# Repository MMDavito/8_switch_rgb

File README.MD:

# Table of contents
- [Table of contents](#table-of-contents)
- [1.1 Introduction:](#11-introduction)
- [1.2 Demonstration:](#12-demonstration)
  - [1.2.1 English:](#121-english)
  - [1.2.1 Swedish:](#121-swedish)
- [2 Design and process:](#2-design-and-process)
  - [2.1 Arduino](#21-arduino)
  - [2.2 KiCad](#22-kicad)
    - [2.2.1 Schematics and details:](#221-schematics-and-details)
      - [2.2.1.1 PCB rev0](#2211-pcb-rev0)
      - [2.2.1.2 PCB rev1](#2212-pcb-rev1)
    - [2.2.2 Custom Footprint SPDT-Switch:](#222-custom-footprint-spdt-switch)
    - [2.2.3 Custom Footprint 7-segment Display:](#223-custom-footprint-7-segment-display)
  - [2.3 FreeCAD](#23-freecad)
- [3 Assembly:](#3-assembly)
  - [3.1 Assembly of frame/stand:](#31-assembly-of-framestand)
  - [3.2 Assembly/soldering of the PCB](#32-assemblysoldering-of-the-pcb)
    - [3.2.1 Resistors required:](#321-resistors-required)
    - [3.2.2 Order of assembly:](#322-order-of-assembly)
- [4 Programming and bootloading:](#4-programming-and-bootloading)
  - [4.1 Bootloading:](#41-bootloading)
  - [4.2 Programming:](#42-programming)
  - [4.3 Programming the MCU for PCB Revision 1:](#43-programming-the-mcu-for-pcb-revision-1)

________________

# 1.1 Introduction:
This project was created to teach my niece the wonders of electricity and programming.
Here is a video trying to give and project overview and explain the process that made me go from 64 bit memory board to a "space-machine":<br>

# 1.2 Demonstration: 
## 1.2.1 English:
Using Revision 0:<br>

## 1.2.1 Swedish:
Better quality than the english one, using PCB revision 1:

___________
# 2 Design and process:
## 2.1 Arduino
No real design was put in here since the issues needing solving where clearly limited and modular in its nature, the process I choose was to solve issues limited in scope and carry out experiments with components in as modular of a manner as possible.
This is how the original prototype described in the video above ended up containing 3 ATmega-328's.

This approach did however result in many .ino files and duplicate code. The decision I made was to keep all of them; this will allow me to return 5-10 years from now and realize my process of thinking and working has changed and how, maybe I will write a book or blog-post about it. 

## 2.2 KiCad
### 2.2.1 Schematics and details:
The only major differences between the two schematics are that I have a filter on the data and clock-lines in revision 1. I also relabeled the decimal-displays from order "dec-2" to "dec-0" starting from upper left corner in revision 0, to the reversed (and ISO-standard) way of counting/indexing from 0 in the upper left corner.

I also left-out the fuse and some other things in order to conserve space.
#### 2.2.1.1 PCB rev0
Will not publish Gerbers because this version should never ever be built or produced, as can be viewed in this 30 second clip:

#### 2.2.1.2 PCB rev1
Gerbers available for order in this directory:
https://github.com/MMDavito/8_switch_rgb/tree/master/KiCad/8_switch_rgb_pcb_revision_1/gerber_to_order

### 2.2.2 Custom Footprint SPDT-Switch:
The SPDT switch was purchased from digikey: https://www.digikey.se/sv/products/detail/adam-tech/SW-T3-2B-A-A3-S1/15284416 <br>
And later electrokit: https://www.electrokit.com/vippomkopplare-sub-miniatyr-1-pol-on-on-lodoron-smts-102

These had to be changed, since the footprints I found where for the larger 6-Amp switch. If I where to refactor the PCB I would probably make the soldering-pads 20% larger for this footprint, or even more if DRC/Design-Rules-Checker would allow it.
The custom footprint can be found here: https://github.com/MMDavito/8_switch_rgb/tree/master/KiCad/resources/Switch_Custom.pretty
### 2.2.3 Custom Footprint 7-segment Display:
The display used was a 14mm CA display purchased in RED here: https://www.electrokit.com/en/led-display-7-seg-14mm-superrod-ca <br>
And green from here: https://www.electrokit.com/en/led-display-7-seg-14mm-gron-ca

The schematics, PCB and footprint label it as a HDSP-511, which is incorrect, buying HDSP-511 would lead to buying a display too tall and wide to fit.
The edited footprint and 3D .step file can be found here:
https://github.com/MMDavito/8_switch_rgb/tree/master/KiCad/resources/HDSP-511Y
## 2.3 FreeCAD
What started as a means to an end of making it simpler to mount the PCB to a piece of plywood ended up resulting in 4 different design for holders and 3-5 different tools for making assembly simpler.

This process and designs are detailed in this readme:
https://github.com/MMDavito/8_switch_rgb/tree/master/FreeCad/README.MD
____________
# 3 Assembly:
## 3.1 Assembly of frame/stand:
More clear information and details about the 3d-printed parts found in the following video can be found in [this readme](./FreeCad/README.MD), section [3.3](./FreeCad/README.MD#33-template-to-mark-drill-holes) and [3.4](./FreeCad/README.MD#34-led-matrix-holder).<br>

## 3.2 Assembly/soldering of the PCB

### 3.2.1 Resistors required:
__1/8 watt resistors:__
* 10kΩ * 14
* 33Ω * 8
  
__1/4 watt resistors:__
* 330Ω * 2
* 220Ω * 8
* 1kΩ * 6

### 3.2.2 Order of assembly:
1. Small resistors (1/8 watt).
2. Big resistors (1/4 watt).
3. 3mm LED:s.
4. Transistors.
5. DIL-holders.
6. Toggle switches.
7. 7-segment displays.
8. DC-plug & screw-terminals.
9. Push-button, crystal & capacitors.
_____________
# 4 Programming and bootloading:
I used this library to allow me to install bootloader and program the ATmega https://github.com/MCUdude/MiniCore
## 4.1 Bootloading:
To get the ATmega328 become programmable one needs to install a bootloader to it:<br><br>
Here is the instruction I used: https://www.instructables.com/How-to-Burn-the-Arduino-BootLoader-on-to-a-AtMega3/

Here is a alternative version: https://www.instructables.com/Burning-the-Bootloader-on-ATMega328-using-Arduino-/

In future I might adjust the board I have made from a prototype-board or order a PCB that allow me to not need a arduino UNO connected with dupont-wires to install the bootloader to the ATmega-328.

## 4.2 Programming:
Somehow I managed to program the board using diagrams and information found on this page:
https://www.instructables.com/USB-to-Serial-TTL-Adapter-to-Program-ATmega328p/

And this video: 
https://youtu.be/tiETAwkxnmw?si=Nhqw3l6RTYwrkvaB

Skimming through above links I realize that neither really shows my process of programming the MCUs, and I should probably order a PCB and create a project to detail this.

Until I find the time for creating that PCB I here bellow attach a picture comparing the breadboard vs with the soldered prototype one.

I later attached the prototype-board to a piece of plywood to make it even more robust.

## 4.3 Programming the MCU for PCB Revision 1:
Using above instructions, load this sketch onto the MCU:
https://github.com/MMDavito/8_switch_rgb/blob/master/troubleshooting_and_revision_1/2024-03-07_8_switch_rgb_pcb_rev1/8_switch_rgb_rev_1_master_control/8_switch_rgb_rev_1_master_control.ino

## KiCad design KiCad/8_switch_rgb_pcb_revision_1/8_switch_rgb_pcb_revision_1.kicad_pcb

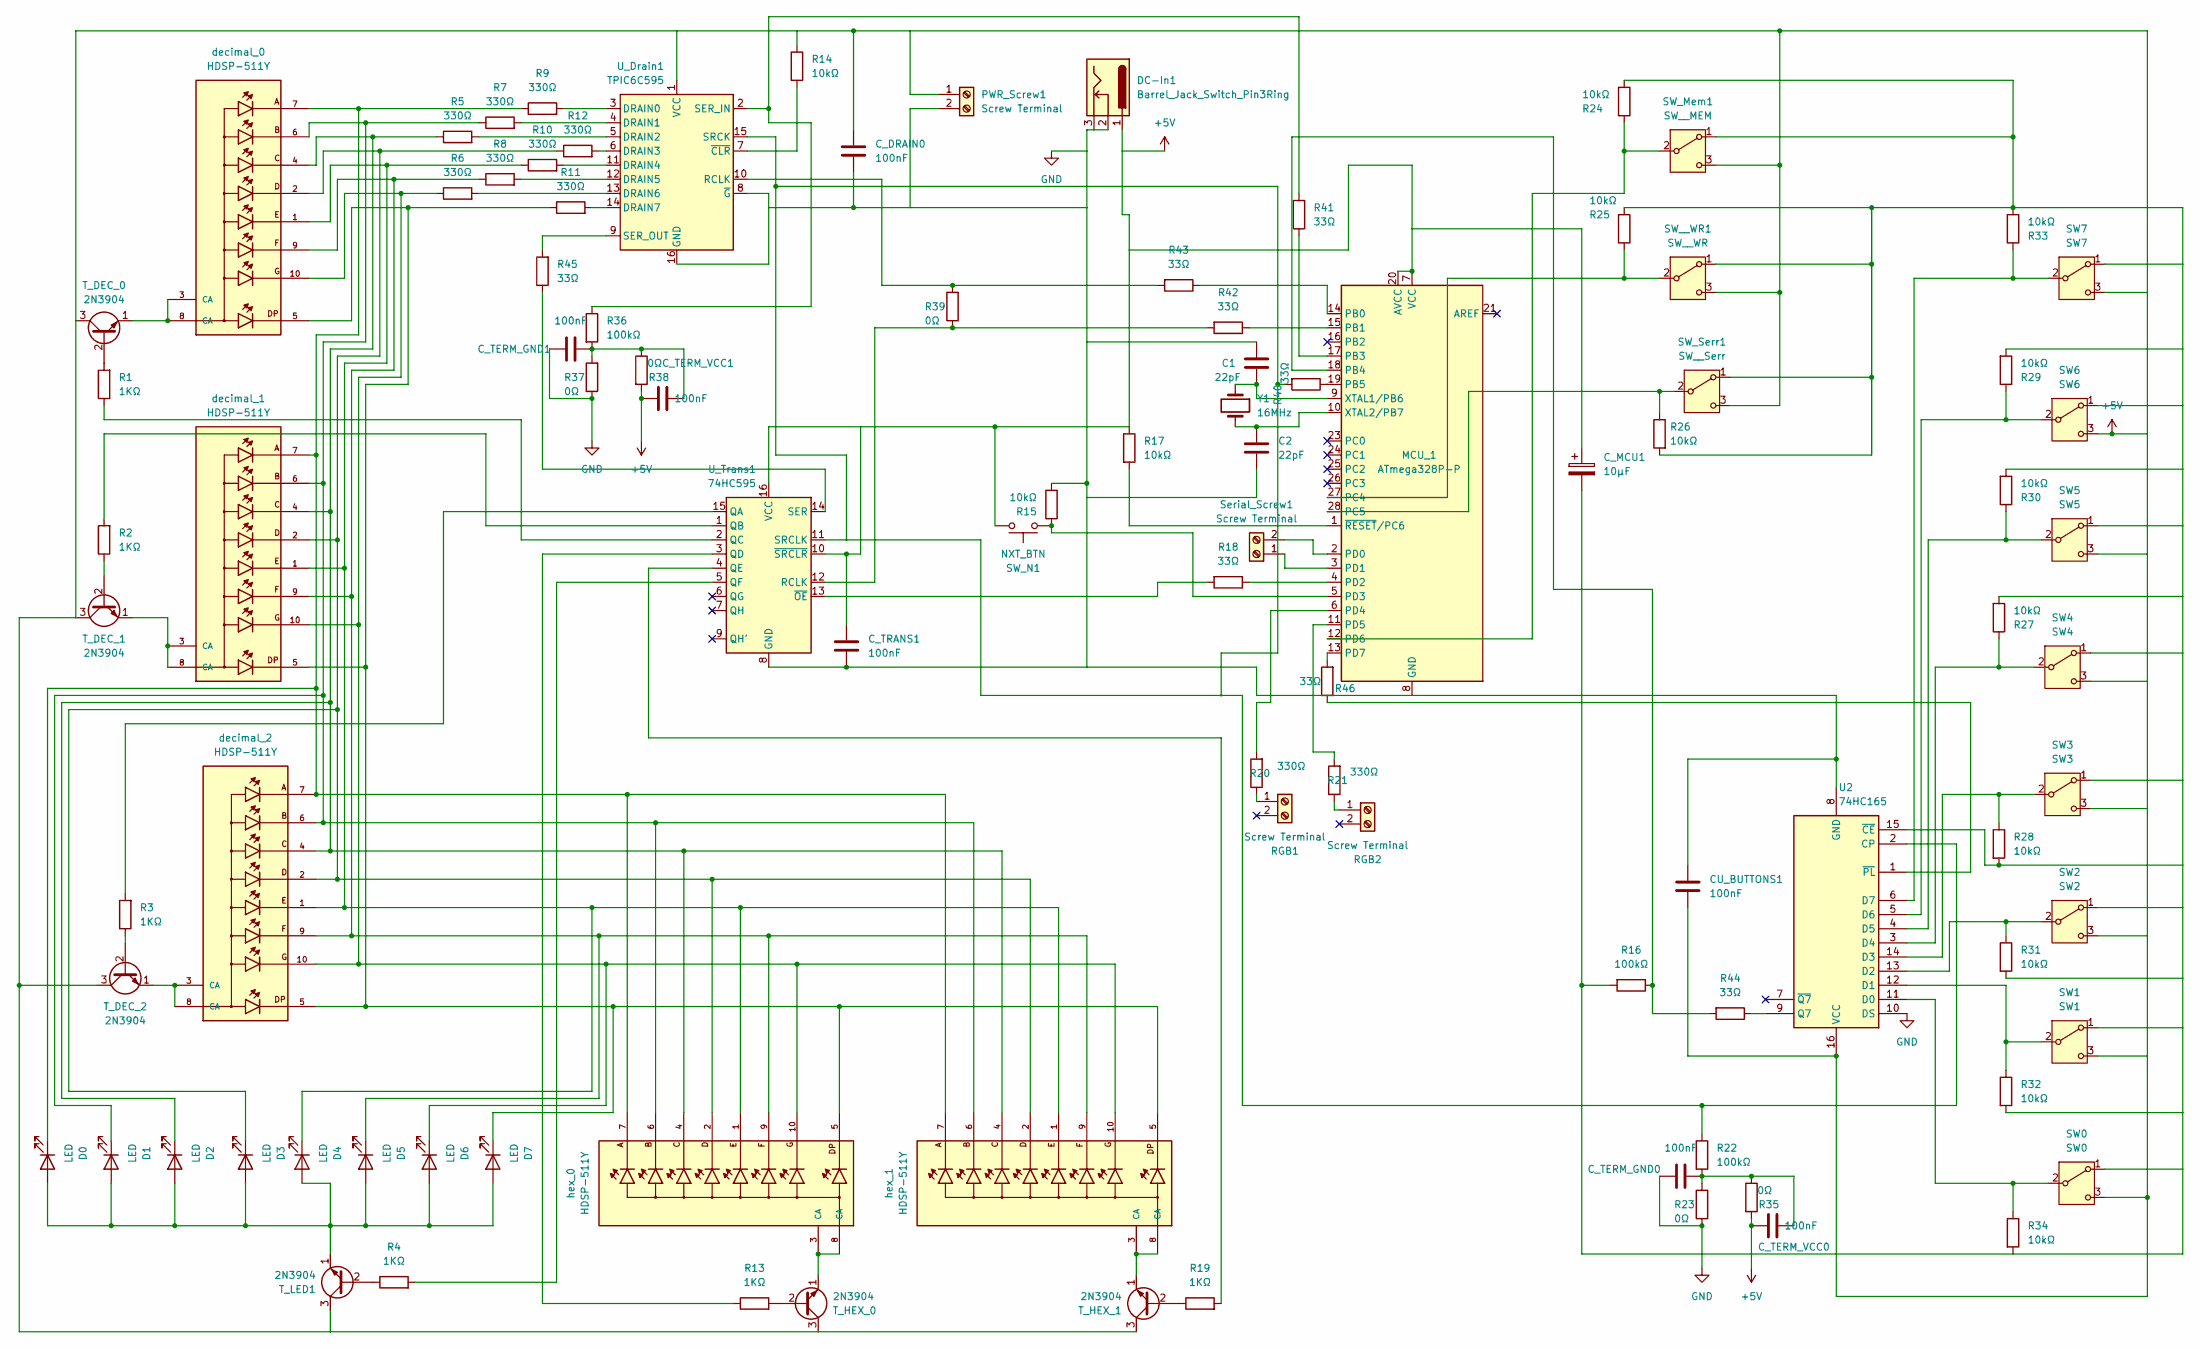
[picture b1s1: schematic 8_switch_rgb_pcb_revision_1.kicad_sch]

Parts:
C1, C2: 22pF; C_Disc_D3.0mm_W1.6mm_P2.50mm
CU_BUTTONS1: 100nF; C_Disc_D5.0mm_W2.5mm_P5.00mm
C_DRAIN0: 100nF; C_Disc_D5.0mm_W2.5mm_P5.00mm
C_MCU1: 10μF; CP_Radial_D4.0mm_P2.00mm
C_TERM_GND0, C_TERM_GND1: 100nF; C_Disc_D5.0mm_W2.5mm_P5.00mm
C_TERM_VCC0, C_TERM_VCC1: 100nF; C_Disc_D5.0mm_W2.5mm_P5.00mm
C_TRANS1: 100nF; C_Disc_D5.0mm_W2.5mm_P5.00mm
D0, D1, D2, D3, D4, D5, D6, D7: LED; LED_D3.0mm
DC-In1: Barrel_Jack_Switch_Pin3Ring; BarrelJack_CUI_PJ-102AH_Horizontal
MCU_1: ATmega328P-P; DIP-28_W7.62mm_Socket
PWR_Screw1: Screw Terminal; TerminalBlock_Phoenix_MPT-0,5-2-2.54_1x02_P2.54mm_Horizontal
R1, R2, R3, R4, R13, R19: 1KΩ; R_Axial_DIN0207_L6.3mm_D2.5mm_P7.62mm_Horizontal
R5, R6, R7, R8, R9, R10, R11, R12, R20, R21: 330Ω; R_Axial_DIN0207_L6.3mm_D2.5mm_P7.62mm_Horizontal
R14, R15, R17, R24, R25, R26, R27, R28, R29, R30, R31, R32, R33, R34: 10kΩ; R_Axial_DIN0204_L3.6mm_D1.6mm_P5.08mm_Horizontal
R16, R22, R36: 100kΩ; R_Axial_DIN0204_L3.6mm_D1.6mm_P5.08mm_Horizontal
R18, R40, R41, R42, R43, R44, R45, R46: 33Ω; R_Axial_DIN0204_L3.6mm_D1.6mm_P5.08mm_Horizontal
R23, R35, R37, R38: 0Ω; R_Axial_DIN0204_L3.6mm_D1.6mm_P2.54mm_Vertical
R39: 0Ω; R_Axial_DIN0204_L3.6mm_D1.6mm_P5.08mm_Horizontal
RGB1, RGB2: Screw Terminal; TerminalBlock_Phoenix_MPT-0,5-2-2.54_1x02_P2.54mm_Horizontal
SW0: SW0; SW_Toggle_Small
SW1: SW1; SW_Toggle_Small
SW2: SW2; SW_Toggle_Small
SW3: SW3; SW_Toggle_Small
SW4: SW4; SW_Toggle_Small
SW5: SW5; SW_Toggle_Small
SW6: SW6; SW_Toggle_Small
SW7: SW7; SW_Toggle_Small
SW_Mem1: SW__MEM; SW_Toggle_Small
SW_N1: NXT_BTN; SW_PUSH_6mm_H5mm
SW_Serr1: SW__Serr; SW_Toggle_Small
SW__WR1: SW__WR; SW_Toggle_Small
Serial_Screw1: Screw Terminal; TerminalBlock_Phoenix_MPT-0,5-2-2.54_1x02_P2.54mm_Horizontal
T_DEC_0, T_DEC_1, T_DEC_2: 2N3904; TO-92_Inline
T_HEX_0, T_HEX_1: 2N3904; TO-92_Inline
T_LED1: 2N3904; TO-92_Inline
U2: 74HC165; DIP-16_W7.62mm_Socket
U_Drain1: TPIC6C595; DIP-16_W7.62mm_Socket
U_Trans1: 74HC595; DIP-16_W7.62mm_Socket
Y1: 16MHz; Crystal_HC49-4H_Vertical
decimal_0, decimal_1, decimal_2: HDSP-511Y; LED_HDSP-511Y; PARTREV April 12, 2021
hex_0, hex_1: HDSP-511Y; LED_HDSP-511Y; PARTREV April 12, 2021

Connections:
+5V: CU_BUTTONS1.2, C_DRAIN0.1, C_MCU1.1, C_TERM_VCC0.2, C_TERM_VCC1.2, C_TRANS1.1, DC-In1.1, MCU_1.7 (VCC), MCU_1.20 (AVCC), PWR_Screw1.1, R14.1, R17.1, R35.2, R38.2, SW0.3 (C), SW1.3 (C), SW2.3 (C), SW3.3 (C), SW4.3 (C), SW5.3 (C), SW6.3 (C), SW7.3 (C), SW_Mem1.3 (C), SW_N1.2, SW_Serr1.3 (C), SW__WR1.3 (C), T_DEC_0.3 (C), T_DEC_1.3 (C), T_DEC_2.3 (C), T_HEX_0.3 (C), T_HEX_1.3 (C), T_LED1.3 (C), U2.16 (VCC), U_Drain1.1 (VCC), U_Trans1.10 (~SRCLR), U_Trans1.16 (VCC)
GND: C1.1, C2.2, CU_BUTTONS1.1, C_DRAIN0.2, C_MCU1.2, C_TERM_GND0.1, C_TERM_GND1.1, C_TRANS1.2, DC-In1.2, DC-In1.3, MCU_1.8 (GND), MCU_1.22 (GND), PWR_Screw1.2, R15.2, R16.2, R23.1, R24.2, R25.2, R26.2, R27.2, R28.2, R29.2, R30.2, R31.2, R32.2, R33.2, R34.2, R37.1, SW0.1 (A), SW1.1 (A), SW2.1 (A), SW3.1 (A), SW4.1 (A), SW5.1 (A), SW6.1 (A), SW7.1 (A), SW_Mem1.1 (A), SW_Serr1.1 (A), SW__WR1.1 (A), U2.8 (GND), U2.10 (DS), U2.15 (~CE), U_Drain1.8 (~G), U_Drain1.16 (GND), U_Trans1.8 (GND)
unnamed: C_TERM_GND0.2, C_TERM_VCC0.1, R22.2, R23.2, R35.1
unnamed: C_TERM_GND1.2, C_TERM_VCC1.1, R36.2, R37.2, R38.1
unnamed: D0.2 (A), D1.2 (A), D2.2 (A), D3.2 (A), D4.2 (A), D5.2 (A), D6.2 (A), D7.2 (A), T_LED1.1 (E)
unnamed: D0.1 (K), R9.1, decimal_0.7, decimal_1.7, decimal_2.7, hex_0.7, hex_1.7
unnamed: D1.1 (K), R7.1, decimal_0.6, decimal_1.6, decimal_2.6, hex_0.6, hex_1.6
unnamed: D2.1 (K), R5.1, decimal_0.4, decimal_1.4, decimal_2.4, hex_0.4, hex_1.4
unnamed: D3.1 (K), R12.1, decimal_0.2, decimal_1.2, decimal_2.2, hex_0.2, hex_1.2
unnamed: D4.1 (K), R10.1, decimal_0.1, decimal_1.1, decimal_2.1, hex_0.1, hex_1.1
unnamed: D5.1 (K), R8.1, decimal_0.9, decimal_1.9, decimal_2.9, hex_0.9, hex_1.9
unnamed: D6.1 (K), R6.1, decimal_0.10, decimal_1.10, decimal_2.10, hex_0.10, hex_1.10
unnamed: D7.1 (K), R11.1, decimal_0.5, decimal_1.5, decimal_2.5, hex_0.5, hex_1.5
unnamed: MCU_1.14 (PB0), R43.1
unnamed: MCU_1.15 (PB1), R42.1
unnamed: MCU_1.17 (PB3), R41.1
unnamed: MCU_1.18 (PB4), R16.1, R44.2
unnamed: MCU_1.19 (PB5), R40.1
unnamed: MCU_1.27 (PC4), R25.1, SW__WR1.2 (B)
unnamed: MCU_1.28 (PC5), R26.1, SW_Serr1.2 (B)
unnamed: MCU_1.2 (PD0), Serial_Screw1.2
unnamed: MCU_1.3 (PD1), Serial_Screw1.1
unnamed: MCU_1.4 (PD2), R18.1
unnamed: MCU_1.5 (PD3), R15.1, SW_N1.1
unnamed: MCU_1.6 (PD4), R20.2
unnamed: MCU_1.11 (PD5), R21.2
unnamed: MCU_1.12 (PD6), R24.1, SW_Mem1.2 (B)
unnamed: MCU_1.13 (PD7), R46.2
unnamed: C1.2, MCU_1.9 (XTAL1/PB6), Y1.1
unnamed: C2.1, MCU_1.10 (XTAL2/PB7), Y1.2
unnamed: MCU_1.1 (~RESET/PC6), R17.2
unnamed: R20.1, RGB1.1
unnamed: R21.1, RGB2.1
unnamed: R34.1, SW0.2 (B), U2.11 (D0)
unnamed: R32.1, SW1.2 (B), U2.12 (D1)
unnamed: R31.1, SW2.2 (B), U2.13 (D2)
unnamed: R28.1, SW3.2 (B), U2.14 (D3)
unnamed: R27.1, SW4.2 (B), U2.3 (D4)
unnamed: R30.1, SW5.2 (B), U2.4 (D5)
unnamed: R29.1, SW6.2 (B), U2.5 (D6)
unnamed: R33.1, SW7.2 (B), U2.6 (D7)
unnamed: R1.2, T_DEC_0.2 (B)
unnamed: T_DEC_0.1 (E), decimal_0.3 (CA), decimal_0.8 (CA)
unnamed: R2.1, T_DEC_1.2 (B)
unnamed: T_DEC_1.1 (E), decimal_1.3 (CA), decimal_1.8 (CA)
unnamed: R3.1, T_DEC_2.2 (B)
unnamed: T_DEC_2.1 (E), decimal_2.3 (CA), decimal_2.8 (CA)
unnamed: R13.2, T_HEX_0.2 (B)
unnamed: T_HEX_0.1 (E), hex_0.3 (CA), hex_0.8 (CA)
unnamed: R19.1, T_HEX_1.2 (B)
unnamed: T_HEX_1.1 (E), hex_1.3 (CA), hex_1.8 (CA)
unnamed: R4.1, T_LED1.2 (B)
unnamed: R22.1, R40.2, U2.2 (CP), U_Drain1.15 (SRCK), U_Trans1.11 (SRCLK)
unnamed: R44.1, U2.9 (Q7)
unnamed: R46.1, U2.1 (~PL)
unnamed: R9.2, U_Drain1.3 (DRAIN0)
unnamed: R7.2, U_Drain1.4 (DRAIN1)
unnamed: R5.2, U_Drain1.5 (DRAIN2)
unnamed: R12.2, U_Drain1.6 (DRAIN3)
unnamed: R10.2, U_Drain1.11 (DRAIN4)
unnamed: R8.2, U_Drain1.12 (DRAIN5)
unnamed: R6.2, U_Drain1.13 (DRAIN6)
unnamed: R11.2, U_Drain1.14 (DRAIN7)
unnamed: R39.2, R43.2, U_Drain1.10 (RCLK)
unnamed: R36.1, R41.2, U_Drain1.2 (SER_IN)
unnamed: R45.2, U_Drain1.9 (SER_OUT)
unnamed: R14.2, U_Drain1.7 (~CLR)
unnamed: R3.2, U_Trans1.15 (QA)
unnamed: R2.2, U_Trans1.1 (QB)
unnamed: R1.1, U_Trans1.2 (QC)
unnamed: R13.1, U_Trans1.3 (QD)
unnamed: R19.2, U_Trans1.4 (QE)
unnamed: R4.2, U_Trans1.5 (QF)
unnamed: R39.1, R42.2, U_Trans1.12 (RCLK)
unnamed: R45.1, U_Trans1.14 (SER)
unnamed: R18.2, U_Trans1.13 (~OE)

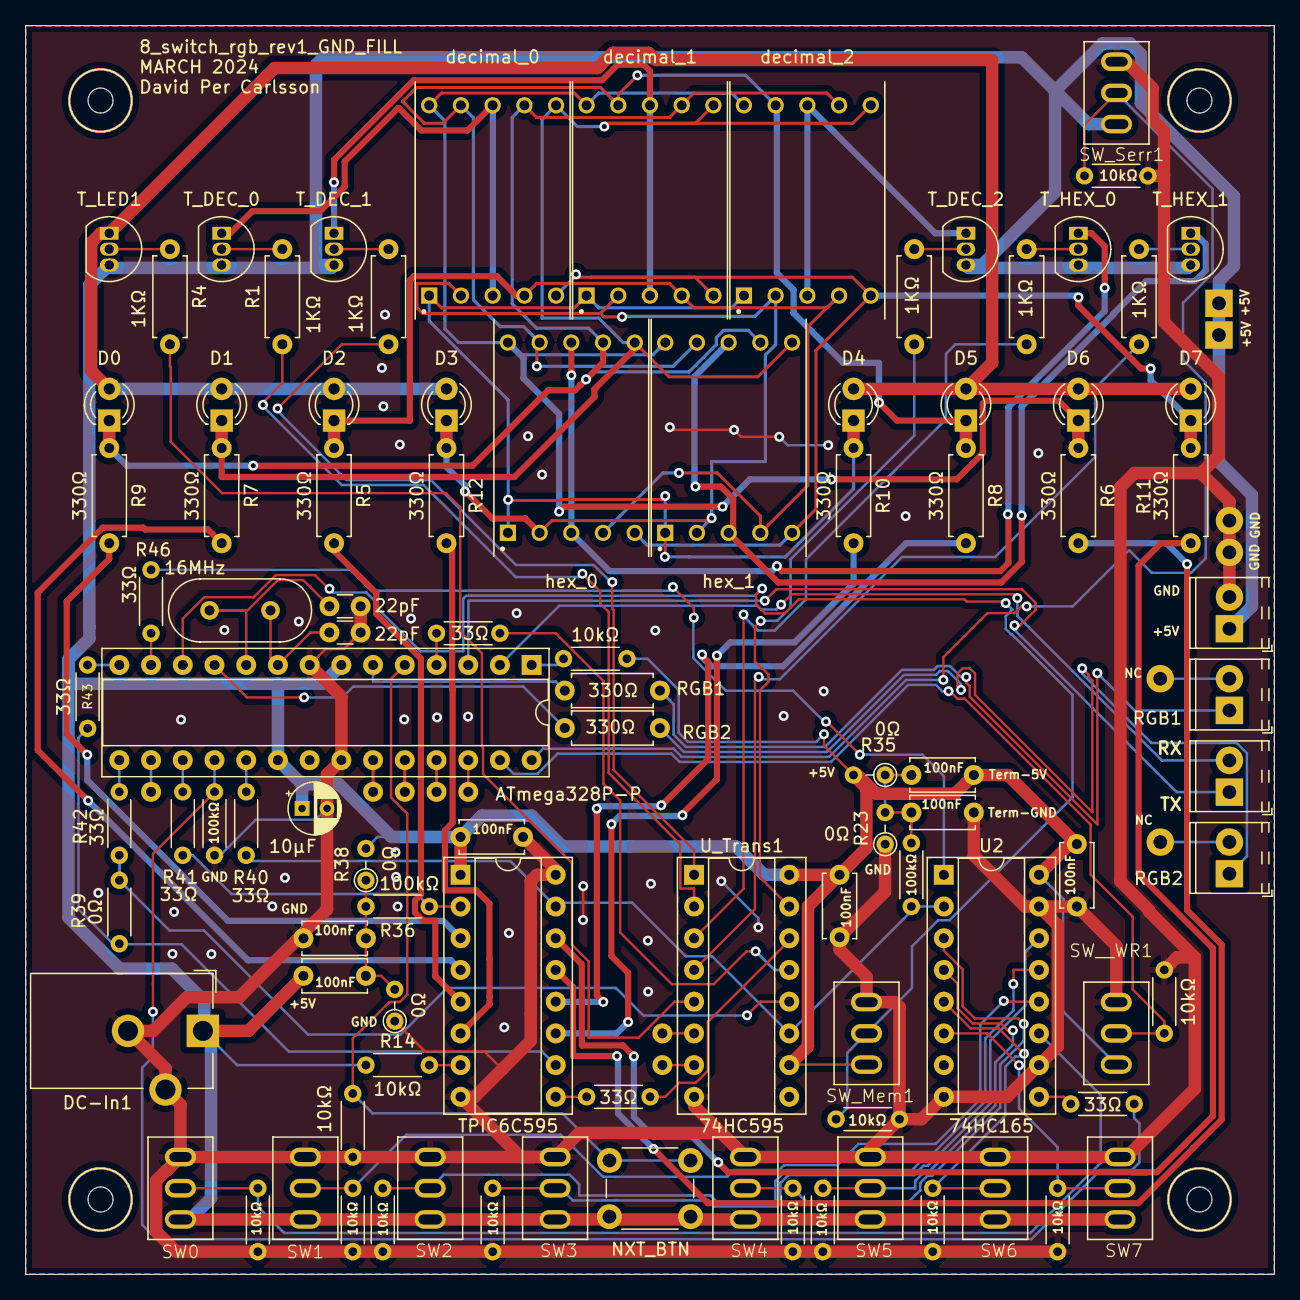
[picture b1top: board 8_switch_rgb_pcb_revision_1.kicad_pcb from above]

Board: 2 copper layers, 100.0 x 100.0 mm, 97 parts (0 on the bottom side), 76 nets.

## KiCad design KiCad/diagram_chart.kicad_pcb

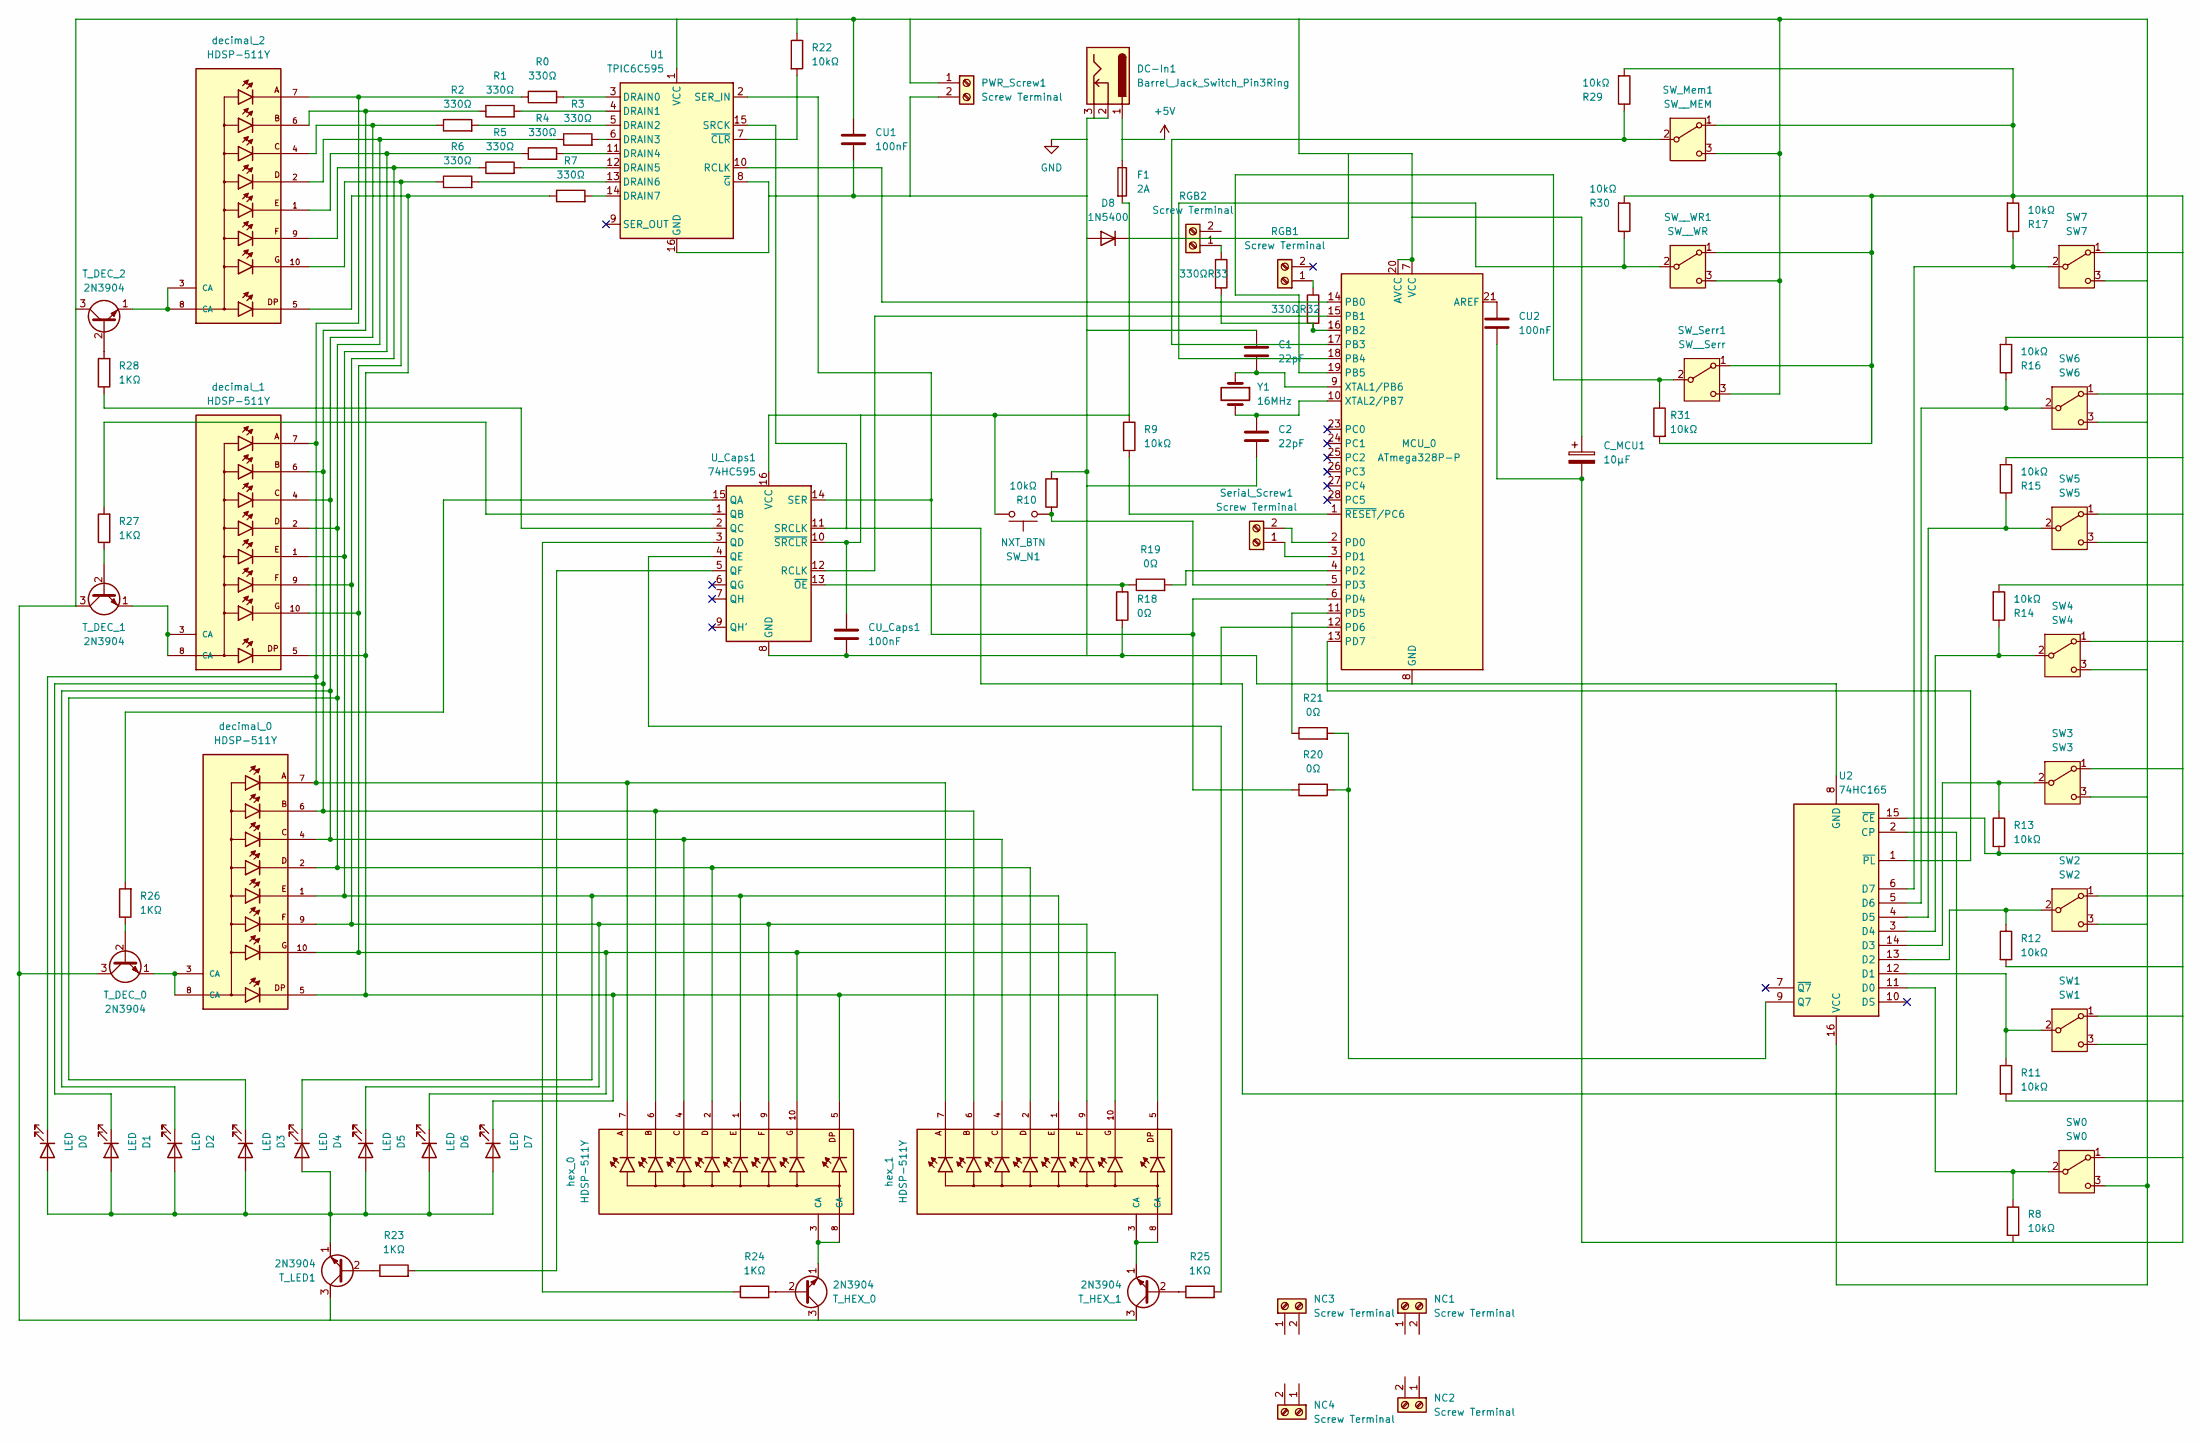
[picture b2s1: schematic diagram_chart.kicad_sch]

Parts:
C1, C2: 22pF; C_Disc_D3.0mm_W1.6mm_P2.50mm
CU1, CU2: 100nF; C_Disc_D3.0mm_W1.6mm_P2.50mm
CU_Caps1: 100nF; C_Disc_D3.0mm_W1.6mm_P2.50mm
C_MCU1: 10μF; CP_Radial_D4.0mm_P2.00mm
D0, D1, D2, D3, D4, D5, D6, D7: LED; LED_D3.0mm
D8: 1N5400; D_DO-201AD_P15.24mm_Horizontal
DC-In1: Barrel_Jack_Switch_Pin3Ring; BarrelJack_CUI_PJ-102AH_Horizontal
F1: 2A; Fuseholder_Clip-5x20mm_Eaton_1A5601-01_Inline_P20.80x6.76mm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
MCU_0: ATmega328P-P; DIP-28_W7.62mm_Socket
NC1, NC2, NC3, NC4: Screw Terminal; TerminalBlock_Phoenix_MPT-0,5-2-2.54_1x02_P2.54mm_Horizontal
PWR_Screw1: Screw Terminal; TerminalBlock_Phoenix_MPT-0,5-2-2.54_1x02_P2.54mm_Horizontal
R0, R1, R2, R3, R4, R5, R6, R7, R32, R33: 330Ω; R_Axial_DIN0207_L6.3mm_D2.5mm_P7.62mm_Horizontal
R8, R9, R10, R11, R12, R13, R14, R15, R16, R17, R22, R29, R30, R31: 10kΩ; R_Axial_DIN0204_L3.6mm_D1.6mm_P5.08mm_Horizontal
R18, R19, R20, R21: 0Ω; R_Axial_DIN0204_L3.6mm_D1.6mm_P2.54mm_Vertical
R23, R24, R25, R26, R27, R28: 1KΩ; R_Axial_DIN0207_L6.3mm_D2.5mm_P7.62mm_Horizontal
RGB1, RGB2: Screw Terminal; TerminalBlock_Phoenix_MPT-0,5-2-2.54_1x02_P2.54mm_Horizontal
SW0: SW0; SW_Toggle_Blue_SMALL
SW1: SW1; SW_Toggle_Blue_SMALL
SW2: SW2; SW_Toggle_Blue_SMALL
SW3: SW3; SW_Toggle_Blue_SMALL
SW4: SW4; SW_Toggle_Blue_SMALL
SW5: SW5; SW_Toggle_Blue_SMALL
SW6: SW6; SW_Toggle_Blue_SMALL
SW7: SW7; SW_Toggle_Blue_SMALL
SW_Mem1: SW__MEM; SW_Toggle_Blue_SMALL
SW_N1: NXT_BTN; SW_PUSH_6mm_H5mm
SW_Serr1: SW__Serr; SW_Toggle_Blue_SMALL
SW__WR1: SW__WR; SW_Toggle_Blue_SMALL
Serial_Screw1: Screw Terminal; TerminalBlock_Phoenix_MPT-0,5-2-2.54_1x02_P2.54mm_Horizontal
T_DEC_0, T_DEC_1, T_DEC_2: 2N3904; TO-92_Inline
T_HEX_0, T_HEX_1: 2N3904; TO-92_Inline
T_LED1: 2N3904; TO-92_Inline
U1: TPIC6C595; DIP-16_W7.62mm_Socket
U2: 74HC165; DIP-16_W7.62mm_Socket
U_Caps1: 74HC595; DIP-16_W7.62mm_Socket
Y1: 16MHz; Crystal_HC49-4H_Vertical
decimal_0, decimal_1, decimal_2: HDSP-511Y; LED_HDSP-511Y; PARTREV April 12, 2021
hex_0, hex_1: HDSP-511Y; LED_HDSP-511Y; PARTREV April 12, 2021

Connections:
+5V: DC-In1.1, F1.1
GND: C1.1, C2.2, CU1.2, CU2.2, CU_Caps1.2, C_MCU1.2, D8.2 (A), DC-In1.2, DC-In1.3, MCU_0.8 (GND), MCU_0.22 (GND), PWR_Screw1.2, R8.2, R10.2, R11.2, R12.2, R13.2, R14.2, R15.2, R16.2, R17.2, R18.2, R29.2, R30.2, R31.2, SW0.1 (A), SW1.1 (A), SW2.1 (A), SW3.1 (A), SW4.1 (A), SW5.1 (A), SW6.1 (A), SW7.1 (A), SW_Mem1.1 (A), SW_Serr1.1 (A), SW__WR1.1 (A), U1.8 (~G), U1.16 (GND), U2.8 (GND), U2.15 (~CE), U_Caps1.8 (GND); also elsewhere on the board
unnamed: D0.2 (A), D1.2 (A), D2.2 (A), D3.2 (A), D4.2 (A), D5.2 (A), D6.2 (A), D7.2 (A), T_LED1.1 (E)
unnamed: D0.1 (K), R0.1, decimal_0.7, decimal_1.7, decimal_2.7, hex_0.7, hex_1.7
unnamed: D1.1 (K), R1.1, decimal_0.6, decimal_1.6, decimal_2.6, hex_0.6, hex_1.6
unnamed: D2.1 (K), R2.1, decimal_0.4, decimal_1.4, decimal_2.4, hex_0.4, hex_1.4
unnamed: D3.1 (K), R3.1, decimal_0.2, decimal_1.2, decimal_2.2, hex_0.2, hex_1.2
unnamed: D4.1 (K), R4.1, decimal_0.1, decimal_1.1, decimal_2.1, hex_0.1, hex_1.1
unnamed: D5.1 (K), R5.1, decimal_0.9, decimal_1.9, decimal_2.9, hex_0.9, hex_1.9
unnamed: D6.1 (K), R6.1, decimal_0.10, decimal_1.10, decimal_2.10, hex_0.10, hex_1.10
unnamed: D7.1 (K), R7.1, decimal_0.5, decimal_1.5, decimal_2.5, hex_0.5, hex_1.5
unnamed 11: CU1.1, CU_Caps1.1, C_MCU1.1, D8.1 (K), F1.2, MCU_0.7 (VCC), MCU_0.20 (AVCC), PWR_Screw1.1, R9.1, R22.1, SW0.3 (C), SW1.3 (C), SW2.3 (C), SW3.3 (C), SW4.3 (C), SW5.3 (C), SW6.3 (C), SW7.3 (C), SW_Mem1.3 (C), SW_N1.2, SW_Serr1.3 (C), SW__WR1.3 (C), T_DEC_0.3 (C), T_DEC_1.3 (C), T_DEC_2.3 (C), T_HEX_0.3 (C), T_HEX_1.3 (C), T_LED1.3 (C), U1.1 (VCC), U2.16 (VCC), U_Caps1.10 (~SRCLR), U_Caps1.16 (VCC); also elsewhere on the board
unnamed: CU2.1, MCU_0.21 (AREF)
unnamed: MCU_0.14 (PB0), U1.10 (RCLK)
unnamed: MCU_0.15 (PB1), U_Caps1.12 (RCLK)
unnamed: MCU_0.16 (PB2), R32.2, R33.2
unnamed: MCU_0.17 (PB3), R29.1, SW_Mem1.2 (B)
unnamed: MCU_0.18 (PB4), R30.1, SW__WR1.2 (B)
unnamed: MCU_0.19 (PB5), R31.1, SW_Serr1.2 (B)
unnamed 19: MCU_0.2 (PD0), Serial_Screw1.2; also elsewhere on the board
unnamed 20: MCU_0.3 (PD1), Serial_Screw1.1; also elsewhere on the board
unnamed: MCU_0.4 (PD2), R19.2
unnamed: MCU_0.5 (PD3), R10.1, SW_N1.1
unnamed: MCU_0.6 (PD4), R20.2, U1.2 (SER_IN), U_Caps1.14 (SER)
unnamed: MCU_0.11 (PD5), R21.1
unnamed: MCU_0.12 (PD6), U1.15 (SRCK), U2.2 (CP), U_Caps1.11 (SRCLK)
unnamed: MCU_0.13 (PD7), U2.1 (~PL)
unnamed: C1.2, MCU_0.9 (XTAL1/PB6), Y1.1
unnamed: C2.1, MCU_0.10 (XTAL2/PB7), Y1.2
unnamed: MCU_0.1 (~RESET/PC6), R9.2
unnamed: R32.1, RGB1.1
unnamed: R33.1, RGB2.1
unnamed: R8.1, SW0.2 (B), U2.11 (D0)
unnamed: R11.1, SW1.2 (B), U2.12 (D1)
unnamed: R12.1, SW2.2 (B), U2.13 (D2)
unnamed: R13.1, SW3.2 (B), U2.14 (D3)
unnamed: R14.1, SW4.2 (B), U2.3 (D4)
unnamed: R15.1, SW5.2 (B), U2.4 (D5)
unnamed: R16.1, SW6.2 (B), U2.5 (D6)
unnamed: R17.1, SW7.2 (B), U2.6 (D7)
unnamed: R26.1, T_DEC_0.2 (B)
unnamed: T_DEC_0.1 (E), decimal_0.3 (CA), decimal_0.8 (CA)
unnamed: R27.1, T_DEC_1.2 (B)
unnamed: T_DEC_1.1 (E), decimal_1.3 (CA), decimal_1.8 (CA)
unnamed: R28.2, T_DEC_2.2 (B)
unnamed: T_DEC_2.1 (E), decimal_2.3 (CA), decimal_2.8 (CA)
unnamed: R24.2, T_HEX_0.2 (B)
unnamed: T_HEX_0.1 (E), hex_0.3 (CA), hex_0.8 (CA)
unnamed: R25.1, T_HEX_1.2 (B)
unnamed: T_HEX_1.1 (E), hex_1.3 (CA), hex_1.8 (CA)
unnamed: R23.1, T_LED1.2 (B)
unnamed: R0.2, U1.3 (DRAIN0)
unnamed: R1.2, U1.4 (DRAIN1)
unnamed: R2.2, U1.5 (DRAIN2)
unnamed: R3.2, U1.6 (DRAIN3)
unnamed: R4.2, U1.11 (DRAIN4)
unnamed: R5.2, U1.12 (DRAIN5)
unnamed: R6.2, U1.13 (DRAIN6)
unnamed: R7.2, U1.14 (DRAIN7)
unnamed: R22.2, U1.7 (~CLR)
unnamed: R20.1, R21.2, U2.9 (Q7)
unnamed: R26.2, U_Caps1.15 (QA)
unnamed: R27.2, U_Caps1.1 (QB)
unnamed: R28.1, U_Caps1.2 (QC)
unnamed: R24.1, U_Caps1.3 (QD)
unnamed: R25.2, U_Caps1.4 (QE)
unnamed: R23.2, U_Caps1.5 (QF)
unnamed: R18.1, R19.1, U_Caps1.13 (~OE)

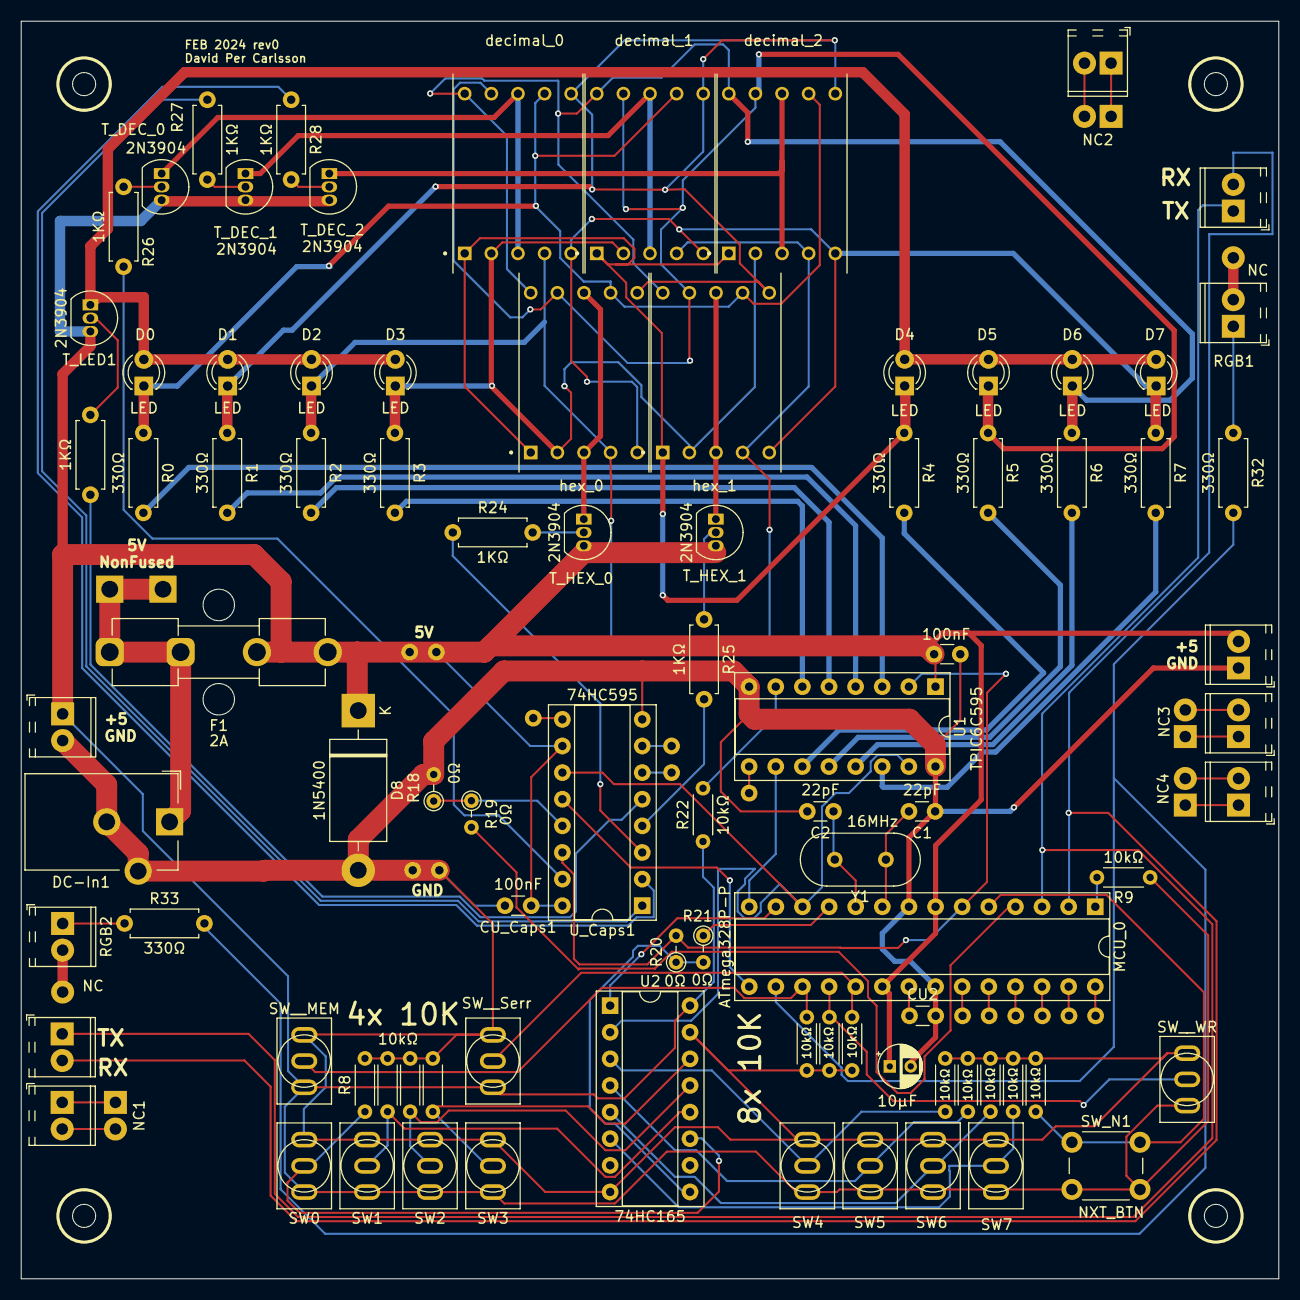
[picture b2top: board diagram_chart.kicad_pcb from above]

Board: 2 copper layers, 120.0 x 120.0 mm, 89 parts (0 on the bottom side), 68 nets.

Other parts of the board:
PWR_Screw2: Screw Terminal; TerminalBlock_Phoenix_MPT-0,5-2-2.54_1x02_P2.54mm_Horizontal
Serial_Screw1#2: Screw Terminal; TerminalBlock_Phoenix_MPT-0,5-2-2.54_1x02_P2.54mm_Horizontal

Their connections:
GND: PWR_Screw2.1; also elsewhere on the board
unnamed 11: PWR_Screw2.2; also elsewhere on the board
unnamed 19: Serial_Screw1#2.2; also elsewhere on the board
unnamed 20: Serial_Screw1#2.1; also elsewhere on the board

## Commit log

2023-10-14 Made the button stable
2023-10-14 Broke it because needed to add bitwise operator to remember
2023-10-15 Added pinout of memorychip
2023-10-29 Wasted 2 hours before realizing NODEmcu lacks pullup-capability. Next step is to get Arduino react to high INPUT
2023-11-02 changed pinconfig, more pedagogical
2023-11-25 Made changes for nodeMCU need ATMega
2023-12-02 setup to handle atmega328p, uploaded
2023-12-02 I am confused look at the dif
2023-12-03 Fixed the bug, also added loging
2023-12-03 Added all switches, also removed todo
2023-12-16 Only print to serial if value is updated
2023-12-16 fixed some things
2023-12-19 Fixed the serial communication to fit that of the hexadecimals
2023-12-19 Removed delay I used for troubleshooting
2023-12-26 Added start of kicad diagram
2024-01-06 Added the configs for bootloader in Arduino IDE
2024-01-07 Added custom footprint and need to look at show to include it
2024-01-07 Added the required Transistors, need to add DC-plug, LEDs and 7-segments
2024-01-07 Added the things I said I would
2024-01-07 Added screw terminals
2024-01-07 Experiments with flipflops
2024-01-07 Verified FlipFlop reset did not need a clock signal
2024-01-07 Will test using QUAD NAND Set-Reset Flip-Flop next week
2024-01-13 Need to git ignore and restructure and create monorepo
2024-01-13 Moved the KiCad things to it's own folder
2024-01-13 Renamed and moved the two projects that was merged to this monorepo
2024-01-14 Restructured some and decided to go with 8mm char height
2024-01-28 Removed backups
2024-01-28 Ignoring backups
2024-01-28 Addewd new barrel-jack and added 14mm 7-segment
2024-01-28 Halfway done with wire-diagram, 90% of components have footprints
2024-02-01 Connected all output-shift registers. Added Caps to ATMega Will need to fix the input-shift-register with switches. Also add Caps, then try to convert to PCB, then call night.
2024-02-01 Added a lot of caps and wires Will try to convert to PCB Will tomorrow need to verrify
2024-02-01 Added NC flags, will now annote everything
2024-02-01 Created PCB. Will need to map traces, and sizes tomorrow. Maybe order tomorrow or more probably tuesday next week.
2024-02-01 Changed from A3 to A4.
    Will make it easier to print PCB and check footprints before ordering.
2024-02-02 Made 14x14 cm. Positioned and alligned switches, displays and LEDs. 1oZ coppar makes me decide for 1mm width per AMP Meaning 0,2mm is enough for 200mA
2024-02-02 Centered the displays to middle Also grouped the entire section
2024-02-02 Added traces, and a lot of VIAS. Not certain about distances from pads, but expensive lessons are the best stucking ones.
2024-02-05 Fixed SPDT to correct sizes. Also flipped them so down is off. Added values of resistors, etc to silkscreen. Made the board 13x13 instead of 14x14. Centralized SPDT sw3, will after lunch center the r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
2024-02-05 Will need to recheck ignored violations tomorrow. DRC checker seems fine. Hole PTH to copper is fine at 0.35mm, not at 0,55. But YOLO
2024-02-06 Verified the footprint seems ok. Ran DRC checker several times.
    I can't claim to be certain of of anything, that would be jinxing.
    But will cross my fingers and order the PCB this afternoon.
2024-02-06 Removed holes from terminal-screws. Obs the gerber files here are not the ones ordered. I will upload zip from pcbway in next commit.
2024-02-06 Ordered via JLCPCB Used GERBERS inside ZIP. Realized it is chinese new years.
2024-02-28 Makeing a revision of the old design. Will focus on heavier GND but also SHORT data/clock and tied to SPI. Also makeing it 10x10cm since cheaper.
2024-02-28 Added pad for serial incase SPI fails.
    Will move the ICs closer together to shorten the serial and clock lines.
2024-02-29 Added 33 ohm series termination resistors. In series with all clock and dataoutputs
2024-02-29 Placed the registers and MCU
    I think it is doable orientation.
2024-02-29 Added all components to board. But the amount of terrible track management is impossible without sleep. I had hopped to be done today, but the remaining tracks and DRC-check will take 2 hours, 4-8 if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
    The important data and clock need to be keept in acute memory.
    Data and clock includes OE and register-clocks.
    I tracked them at the verry begining, so it should be fine.
    Just need to be REALLY careful.
2024-03-01 Made GND 1 mm, aswell as 5v. Will Maybe fill the entire plane with GND at the end.
    Depends how saddened the DRC will make me.
2024-03-01 Connected all traces. Will now run DRC This is the last 2-layer board with more than 10 components I ever create.
2024-03-01 Added 3d And moved dot marking the orintation of 7-seg to within footprint.
2024-03-01 Added gerbers, will look at ground plane
2024-03-01 Added the zip from pcbway. Will order both with ground fill and without
2024-03-01 I guess it is good to add a gitignore. But please look at previous commit. I here added screenshot of 3d with ground_plane
2024-03-02 Added some PDFs Realized the distance between the data line and the gnd for the pulldown resistor for data in from the 74hc165 is way too small, but can't do nothing about that now. It is two differe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
    Still ugly 45+45 degree angle within 2mm
2024-03-02 Added screenshots of PCB layout
2024-03-02 Added draft of a holder in 3d.
2024-03-02 Added hexagon for m3 nut
2024-03-02 Made everything thinner, will try even thinner. Maybe even 8x8 hole in middle.
2024-03-03 Dont know why hexagon dont work
2024-03-04 Made a working 3d. It costs roughly 5 USD each from jlc3dp
2024-03-04 Made some analysises. 5_mm_inc_pcb.stl is probably final version of the holder
2024-03-04 Ordered 3d from jlc3dp
2024-03-05 Made smaler version, but several larger. 2mm Walls was recommended at JLCPCB
2024-03-08 Found the cause of incorrect order of decimals.
2024-03-13 Created holders to support 12mm plywood. Also one to display the noicy 120mm rev_0
2024-03-13 Made corners of big holder square and bigger
2024-03-13 Added tool for 1/8 and 1/4 watt resistors
2024-03-13 Made tools to assemble LED matrixes 5x5 at a time
2024-03-13 Need to organize this better next week. After recieving all prints.
2024-03-16 Found out why JLC3DP complained Regarding wall thickness, it was the 0.5mm pockets. The Resistor leg bender, I ordered without sanding, will see how solid it becomes
2024-04-03 Made resistor value visible in silkscreen. Being the only major issue I discovered during assembly I call it done.
    Also included exports for gerber-files using plugin "GerbersToOrder"
    I could ofc have made 330 ohm current limiting resistors 220, and also
    removed the filters, and made the button location more spacey.
    But I need to finish good enough for now.
2024-04-04 Added readme Finished draft for the most important areas. Left is to explain how to bootload and some other findings and polishing.
    Also deleted the Gerbers for revision-0
2024-04-04 Changed the youtube links. From embedded to hardcoded
2024-04-04 Added more information to the readme. About loading bootloader and programs onto the atmega
    Will next need to describe what .ino to load to the atmega328 for
    revision 1 to work.
    After this I will make the contents of the readme in the freecad folder
    understandable.
2024-04-04 Added reference to the sketch for PCB_mcu_rev1. I realized after a short walk that it's better to continue tomorrow with the contents of the freecad readme. I will tomorrow also need to review the sk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
    Then ask for reviews to maybe clarify possible confusion or insanity of
    the repo.
    But I feel I then need to call quits on this project; only thing
    reminding is the fun/rewarding things of assembling, adding assembly instructions
    and gifting it/delivering to the end-user.
    But now food and sleep.
2024-04-05 Cleaned the cadfiles Also finished 80+% of the CAD readme. Need to eat, then finish the other readme, then finish this one I just started.
2024-04-05 Added todo of what I think remains.
    Again, time for food.
2024-04-05 I think this solves the first part of the todo.
2024-04-05 Corrected spelling
2024-04-05 Updated the todo
2024-04-05 Fixed the things the todo told me to. Also fixed some spelling.
2024-04-19 Added links to video about assembling of stand. Also adding details about 3d-printed tools used in this assembly.
2024-06-03 Update README.MD
    Assembly-video of PCB is filmed, only editing remains.
2024-06-05 Corrected a const that was volatile, also made useage of "volatile" consistent. Realized I lack basic C best-practices, examples: 1. Optimized useage of "volatile" 2. Naming conventions (mostly just 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
2024-06-05 Made the LED-strip be possible to mount reversed order
2024-06-11 Made the green/hex-display more bright. This was achived by decreasing the duty-cycle of the other displays.
2024-06-22 Added ability to use a second RGB_Strip. This RGB-strip is now length 4 and allows so display Red Green Blue and combined color/channel values.
2024-08-22 Added links to videos covering certain areas.
2024-08-22 Corrected grammar, removed todo.
2024-09-07 Added the final notes to finalize the project. These (hopefully) final notes will/would help me if I need to assemble or redo anything.
